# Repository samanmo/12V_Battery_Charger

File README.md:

# 12V Half-Bridge LLC Battery Charger | KiCad Designer

A high-efficiency **12V battery charger** designed for **240V AC mains input**, utilizing a Power Factor Correction (PFC) front-end and a Half-Bridge LLC resonant converter controlled by an STM32 microcontroller.

> **⚠️ HIGH VOLTAGE WARNING:** This design interfaces directly with 240V AC mains and generates lethal high-voltage DC buses. Do not build, test, or probe this hardware unless you are qualified to work with high-voltage power electronics and follow proper isolation procedures (e.g., using an isolation transformer and differential probes).

---

## Key Features & Architecture

Based on the hierarchical schematic blocks in this repository, the power stage and control architecture include:

* **AC Input & EMI Filtering (`emf_filter.kicad_sch`):** Mains input protection, inrush current limiting (NTC/PTC), varistors, and common/differential mode chokes.
* **Half-Bridge LLC Resonant Stage (`llc_power.kicad_sch`):** High-frequency resonant tank with custom transformer and isolated gate drivers (`UCC256404`).
* **Secondary Rectification & Output (`secondary_power.kicad_sch`, `output_filtering.kicad_sch`, `output_protection.kicad_sch`):** Secondary rectification, LC output filtering, and reverse polarity / over-voltage / over-current protection (`ACS720` current sensing).
* **Auxiliary & Bias Power (`auxiliary_power.kicad_sch`, `bias_power_supply.kicad_sch`):** Dedicated auxiliary supplies powering primary and secondary control ICs.
* **Digital Control & Monitoring (`STM32Controller.kicad_sch`, `temperature_sensing.kicad_sch`):** STM32-based PWM generation, charging profile control (CC/CV), and thermal monitoring.

---

## Repository Structure

```text
├── 2025_11_17_ver6.0.kicad_pro    # Main KiCad project file
├── 2025_11_17_ver6.0.kicad_sch    # Root hierarchical schematic
├── 2025_11_17_ver6.0.kicad_pcb    # Main PCB layout
├── *.kicad_sch                    # Hierarchical sub-schematics (PFC, LLC, STM32, etc.)
├── *.kicad_sym                    # Project-specific custom symbol libraries
├── *.pretty/                      # Project-specific custom footprint libraries
├── sym-lib-table & fp-lib-table   # Local library path mappings
├── BatteryCharger_pdf/            # Exported schematic/documentation PDFs
├── 2025_11_17_ver6.0.xlsx         # Bill of Materials (BOM)
└── Design Rules.txt               # PCB layout & clearance design rules
```

---

## Getting Started

1. **Clone the repository:**
   ```bash
   git clone https://github.com/samanmo/12V_Battery_Charger.git
   ```
2. **Open in KiCad:**
   * Launch KiCad and open `2025_11_17_ver6.0.kicad_pro`.
   * All custom symbols (`.kicad_sym`) and footprints (`.pretty`) are stored locally inside the repository and mapped via `sym-lib-table` and `fp-lib-table`.

---

## Renders & Schematics
<!-- 
*(Tip: Export a 3D render from KiCad's 3D Viewer as `docs/pcb_3d.png` and uncomment the line below to display it here)*
-->
<!--  -->

* Full schematic PDFs are available in the [`BatteryCharger_pdf/`](./BatteryCharger_pdf) directory.

---

## License

This project is licensed under the **MIT License** — see the [LICENSE](./LICENSE) file for details.

# 12V ハーフブリッジLLC バッテリーチャージャー
240V AC商用電源入力向けに設計された高効率な12Vバッテリーチャージャーです。力率改善（PFC）フロントエンドと、STM32マイクロコントローラによって制御されるハーフブリッジLLC共振コンバータを採用しています。
> **⚠️ 高電圧に関する警告:**  本設計は240V AC商用電源に直接接続され、致死的な高電圧DCバスを生成します。高電圧パワーエレクトロニクスを取り扱う資格を有し、適切な絶縁手順（絶縁トランスや差動プローブの使用など）を遵守できる場合を除き, 本ハードウェアの製作、テスト、またはプロービングを行わないでください。

---

## 主な特徴とアーキテクチャ
本リポジトリ内の階層型回路図ブロックに基づく、パワーステージおよび制御アーキテクチャの構成は以下の通りです：

* **AC入力およびEMIフィルタリング (emf_filter.kicad_sch)：** 商用電源入力保護、突入電流制限（NTC/PTC）、バリスタ、およびコモンモード／ノーマルモードチョークコイルを備えています。

* **ハーフブリッジLLC共振ステージ (llc_power.kicad_sch)：** カスタムトランスと絶縁型ゲートドライバ（UCC256404）を使用した高周波共振タンクです。

* **二次側整流および出力 (secondary_power.kicad_sch, output_filtering.kicad_sch, output_protection.kicad_sch)：** 二次側整流、LC出力フィルタリング、および逆接続・過電圧・過電流保護（ACS720電流センシング）を搭載しています。

* **補助電源およびバイアス電源 (auxiliary_power.kicad_sch, bias_power_supply.kicad_sch)：** 一次側および二次側の制御ICに電力を供給する専用の補助電源です。

* **デジタル制御および監視 (STM32Controller.kicad_sch, temperature_sensing.kicad_sch)：** STM32ベースのPWM生成、充電プロファイル制御（CC/CV）、および温度監視を行います。

## リポジトリ構成

```text
├── 2025_11_17_ver6.0.kicad_pro    # メインKiCadプロジェクトファイル
├── 2025_11_17_ver6.0.kicad_sch    # ルート階層回路図
├── 2025_11_17_ver6.0.kicad_pcb    # メインPCBレイアウト
├── *.kicad_sch                    # 階層サブ回路図（PFC、LLC、STM32など）
├── *.kicad_sym                    # プロジェクト固有のカスタムシンボルライブラリ
├── *.pretty/                      # プロジェクト固有のカスタムフットプリントライブラリ
├── sym-lib-table & fp-lib-table   # ローカルライブラリパスマッピング
├── BatteryCharger_pdf/            # エクスポートされた回路図・ドキュメントPDF
├── 2025_11_17_ver6.0.xlsx         # 部品表（BOM）
└── Design Rules.txt               # PCBレイアウトおよびクリアランス設計ルール

---

## はじめに
1. **リポジトリのクローン：**
```bash
	git clone https://github.com
```

2. **KiCadで開く：**
	* KiCadを起動し、2025_11_17_ver6.0.kicad_pro を開きます。
	* すべてのカスタムシンボル（.kicad_sym）およびフットプリント（.pretty）はリポジトリ内にローカル保存されており、sym-lib-table および fp-lib-table を介してマッピングされています。
---

## レンダリングと回路図
	* 完全な回路図PDFは BatteryCharger_pdf/ ディレクトリにあります。

---
## ライセンス (License)

このプロジェクトは [MITライセンス](LICENSE) の下で公開されています。

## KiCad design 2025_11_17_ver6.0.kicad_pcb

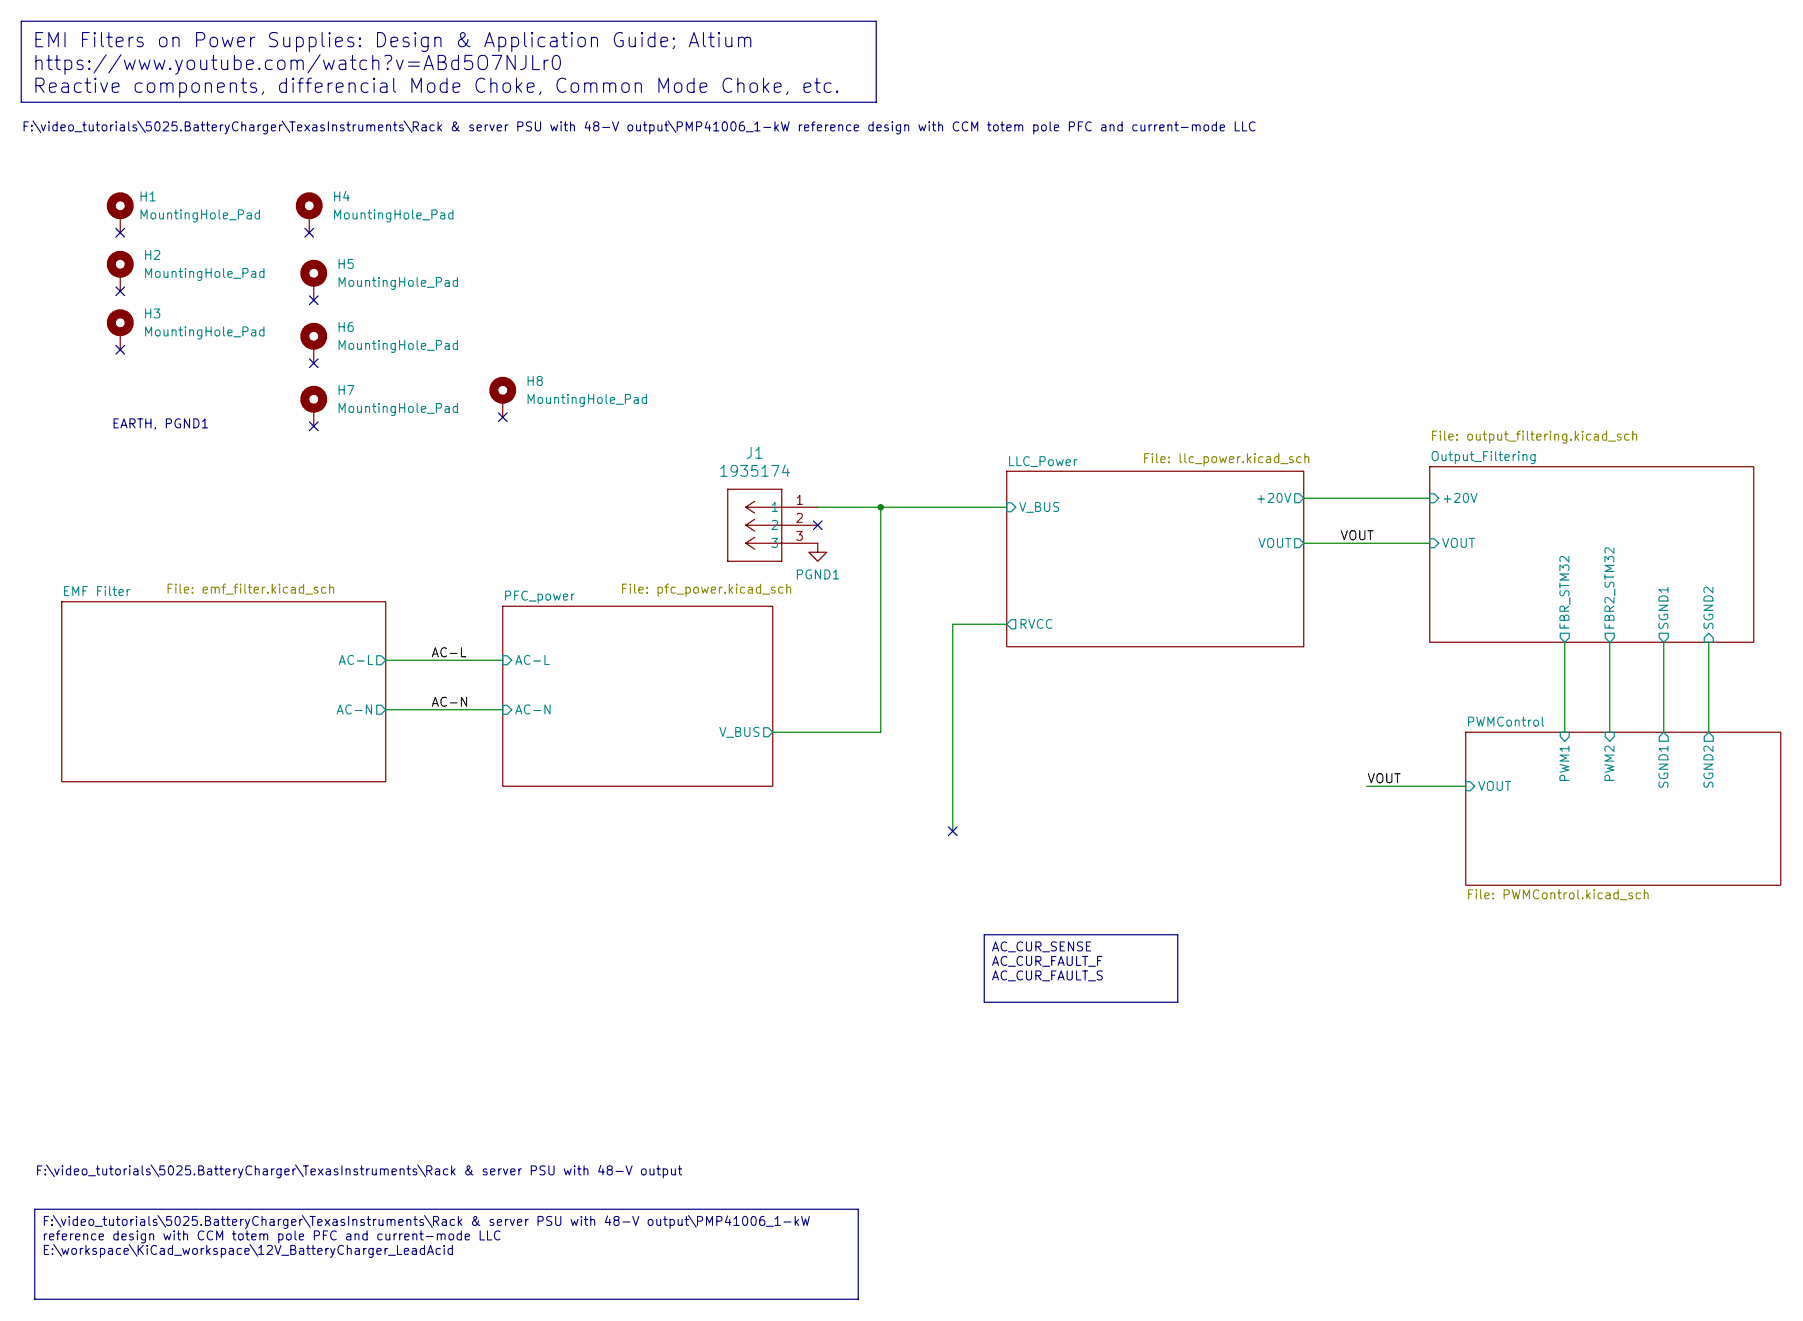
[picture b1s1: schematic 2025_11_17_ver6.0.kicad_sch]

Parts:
H1, H2, H3, H4, H5, H6, H7, H8: MountingHole_Pad; MountingHole_3mm_Pad
J1: 1935174; CONN_1935174_PXC; Manufacturer_Part_Number 1935174; Digi-Key_PN 277-1578-ND

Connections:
/LLC_Power/V_BUS: J1.1; also elsewhere on the board
PGND1: J1.3; also elsewhere on the board

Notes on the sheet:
F:\video_tutorials\5025.BatteryCharger\TexasInstruments\Rack & server PSU with 48-V output
EARTH, PGND1
F:\video_tutorials\5025.BatteryCharger\TexasInstruments\Rack & server PSU with 48-V output\PMP41006_1-kW reference design with CCM totem pole PFC and current-mode LLC
AC_CUR_SENSE AC_CUR_FAULT_F AC_CUR_FAULT_S
F:\video_tutorials\5025.BatteryCharger\TexasInstruments\Rack & server PSU with 48-V output\PMP41006_1-kW reference design with CCM totem pole PFC and current-mode LLC E:\workspace\KiCad_workspace\12V_BatteryCharger_LeadAcid
EMI Filters on Power Supplies: Design & Application Guide; Altium https://www.youtube.com/watch?v=ABd5O7NJLr0 Reactive components, differencial Mode Choke, Common Mode Choke, etc.

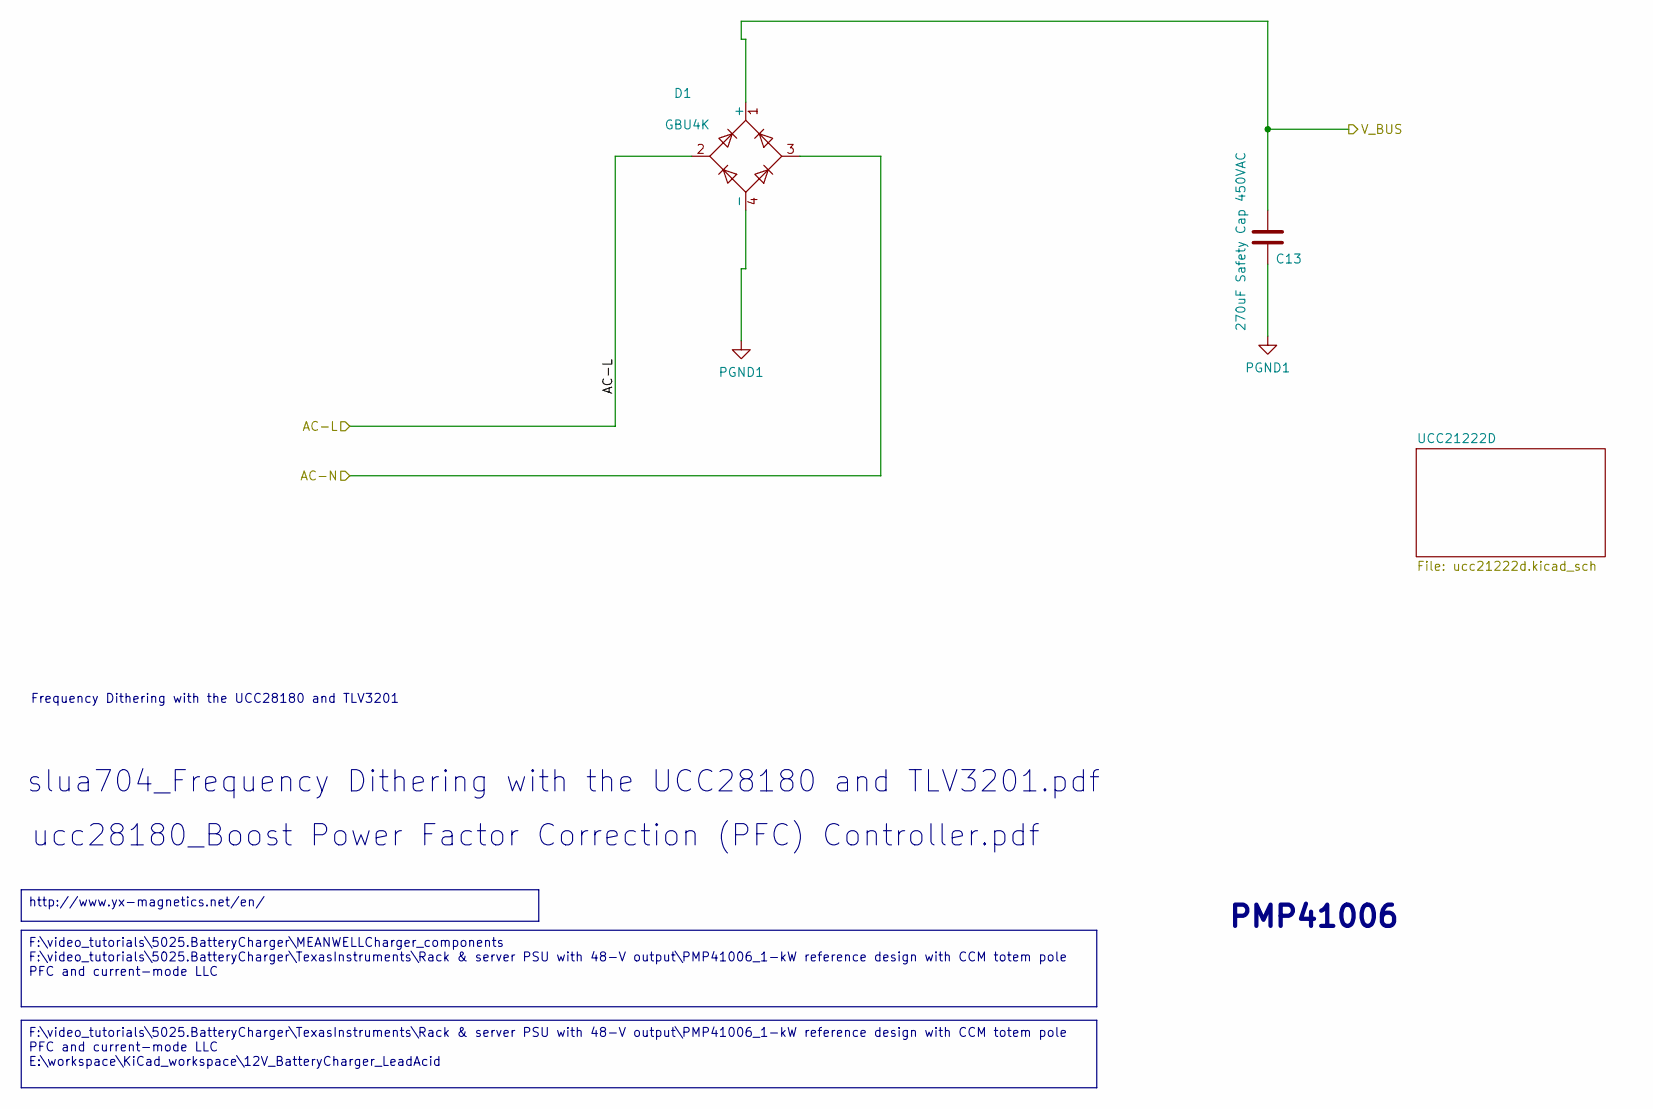
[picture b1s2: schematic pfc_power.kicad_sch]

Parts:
C13: 270uF Safety Cap 450VAC; CP_Radial_D22.0mm_P10.00mm_SnapIn; Mouser Part Number 871-B32923C3155M189; Digi-Key_PN 495-4938-1-ND
D1: GBU4K; Diode_Bridge_Vishay_GBU; Manufacturer_Part_Number GBU4K-E3/45; Digi-Key_PN GBU4K-E3/45GI-ND

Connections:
/AC-L: D1.2; also elsewhere on the board
/AC-N: D1.3; also elsewhere on the board
/LLC_Power/V_BUS: C13.1, D1.1 (+); also elsewhere on the board
PGND1: C13.2, D1.4 (-); also elsewhere on the board

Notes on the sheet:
PMP41006
ucc28180_Boost Power Factor Correction (PFC) Controller.pdf
slua704_Frequency Dithering with the UCC28180 and TLV3201.pdf
Frequency Dithering with the UCC28180 and TLV3201
F:\video_tutorials\5025.BatteryCharger\MEANWELLCharger_components F:\video_tutorials\5025.BatteryCharger\TexasInstruments\Rack & server PSU with 48-V output\PMP41006_1-kW reference design with CCM totem pole PFC and current-mode LLC
http://www.yx-magnetics.net/en/
F:\video_tutorials\5025.BatteryCharger\TexasInstruments\Rack & server PSU with 48-V output\PMP41006_1-kW reference design with CCM totem pole PFC and current-mode LLC E:\workspace\KiCad_workspace\12V_BatteryCharger_LeadAcid

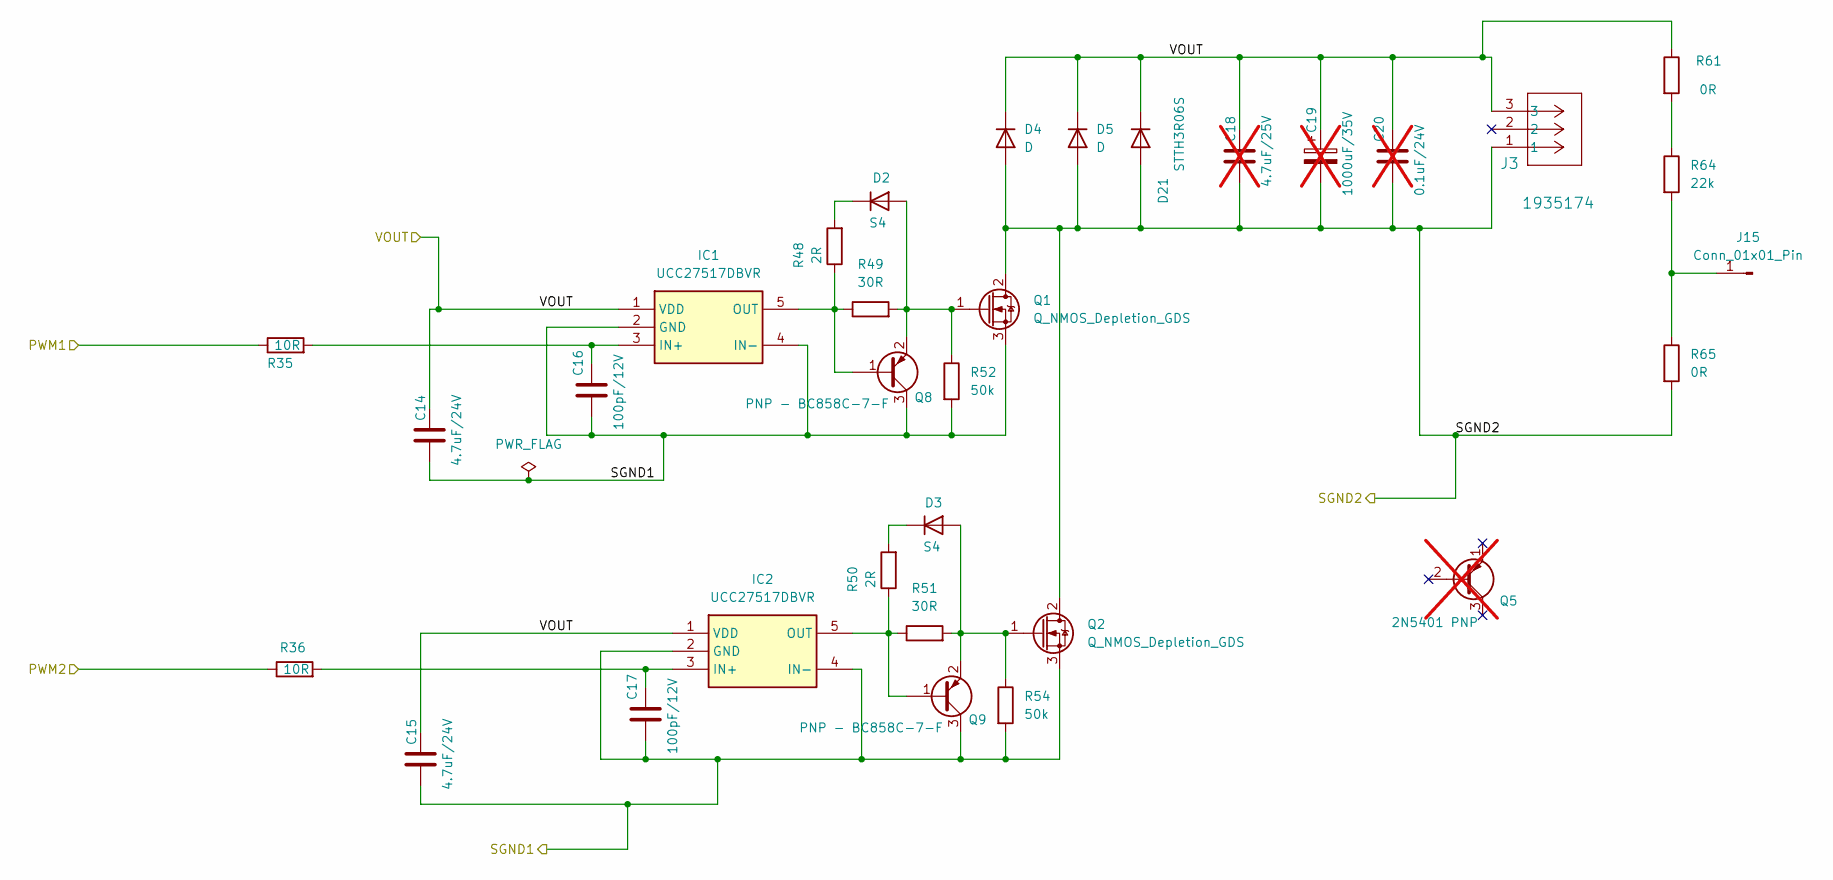
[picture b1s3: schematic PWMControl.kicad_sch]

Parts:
C14, C15: 4.7uF/24V; C_0805_2012Metric_Pad1.18x1.45mm_HandSolder; Manufacturer_Part_Number GRT21BR61H475KE13L; Digi-Key_PN 490-12394-1-ND
C16, C17: 100pF/12V; C_0805_2012Metric_Pad1.18x1.45mm_HandSolder; Manufacturer_Part_Number CC0805KRX7R9BB104; Digi-Key_PN 311-1140-1-ND
C18: 4.7uF/25V; C_0805_2012Metric_Pad1.18x1.45mm_HandSolder; Manufacturer_Part_Number GRT21BR61H475KE13L; Digi-Key_PN 490-12394-1-ND; not fitted
C19: 1000uF/35V; C_Radial_D12.5mm_H25.0mm_P5.00mm; Manufacturer_Part_Number ECA-1HM102; Digi-Key_PN P5186-ND; not fitted
C20: 0.1uF/24V; C_0805_2012Metric_Pad1.18x1.45mm_HandSolder; Manufacturer_Part_Number CC0805KRX7R9BB104; Digi-Key_PN 311-1140-1-ND; not fitted
D2, D3: S4; D_0805_2012Metric_Pad1.15x1.40mm_HandSolder; Manufacturer_Part_Number BAS316Z; Digi-Key_PN 1727-7370-1-ND
D4, D5: D; D_SMA_Handsoldering
D21: STTH3R06S; D_SMC_Handsoldering; Manufacturer_Part_Number STTH3R06S; Digi-Key_PN 497-3779-1-ND
IC1, IC2: UCC27517DBVR; SOT-23-5_HandSoldering; Mouser Part Number 595-UCC27517DBVR
J3: 1935174; TerminalBlock_Phoenix_PT-1,5-3-5.0-H_1x03_P5.00mm_Horizonta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; Manufacturer_Part_Number 1935174; Digi-Key_PN 277-1578-ND
J15: Conn_01x01_Pin; PinHeader_1x01_P2.54mm_Vertical
Q1, Q2: Q_NMOS_Depletion_GDS; TO-220-3_Vertical
Q5: 2N5401 PNP; TO-92L_Inline_Wide; not fitted
Q8, Q9: PNP - BC858C-7-F; SOT-23; Manufacturer_Part_Number BC858C-7-F; Digi-Key_PN 31-BC858C-7-FCT-ND
R35, R36: 10R; R_0805_2012Metric_Pad1.20x1.40mm_HandSolder
R48, R50: 2R; R_1206_3216Metric_Pad1.30x1.75mm_HandSolder; Manufacturer_Part_Number RT1206DRE0710RL; Digi-Key_PN 311-2958-1-ND
R49, R51: 30R; R_1206_3216Metric_Pad1.30x1.75mm_HandSolder
R52, R54: 50k; R_0805_2012Metric_Pad1.20x1.40mm_HandSolder
R61, R65: 0R; R_0805_2012Metric_Pad1.20x1.40mm_HandSolder
R64: 22k; R_0805_2012Metric_Pad1.20x1.40mm_HandSolder

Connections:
/Output_Filtering/FBR2_STM32: R36.1; also elsewhere on the board
/Output_Filtering/FBR_STM32: R35.1; also elsewhere on the board
/Output_Filtering/SGND1: C14.2, C15.2, C16.2, C17.2, IC1.2 (GND), IC1.4 (IN-), IC2.2 (GND), IC2.4 (IN-), Q1.3 (S), Q2.3 (S), Q8.3 (C), Q9.3 (C), R52.2, R54.2; also elsewhere on the board
/Output_Filtering/SGND2: C18.2, C19.2, C20.2, D4.2 (A), D5.2 (A), D21.2 (A), J3.1, Q1.2 (D), Q2.2 (D), R65.2; also elsewhere on the board
/VOUT: C14.1, C15.1, C18.1, C19.1, C20.1, D4.1 (K), D5.1 (K), D21.1 (K), IC1.1 (VDD), IC2.1 (VDD), J3.3, R61.1; also elsewhere on the board
unnamed: D2.2 (A), Q1.1 (G), Q8.2 (E), R49.2, R52.1
unnamed: D2.1 (K), R48.2
unnamed: D3.2 (A), Q2.1 (G), Q9.2 (E), R51.2, R54.1
unnamed: D3.1 (K), R50.2
unnamed: C16.1, IC1.3 (IN+), R35.2
unnamed: IC1.5 (OUT), Q8.1 (B), R48.1, R49.1
unnamed: C17.1, IC2.3 (IN+), R36.2
unnamed: IC2.5 (OUT), Q9.1 (B), R50.1, R51.1
unnamed: J15.1, R64.2, R65.1
unnamed: R61.2, R64.1

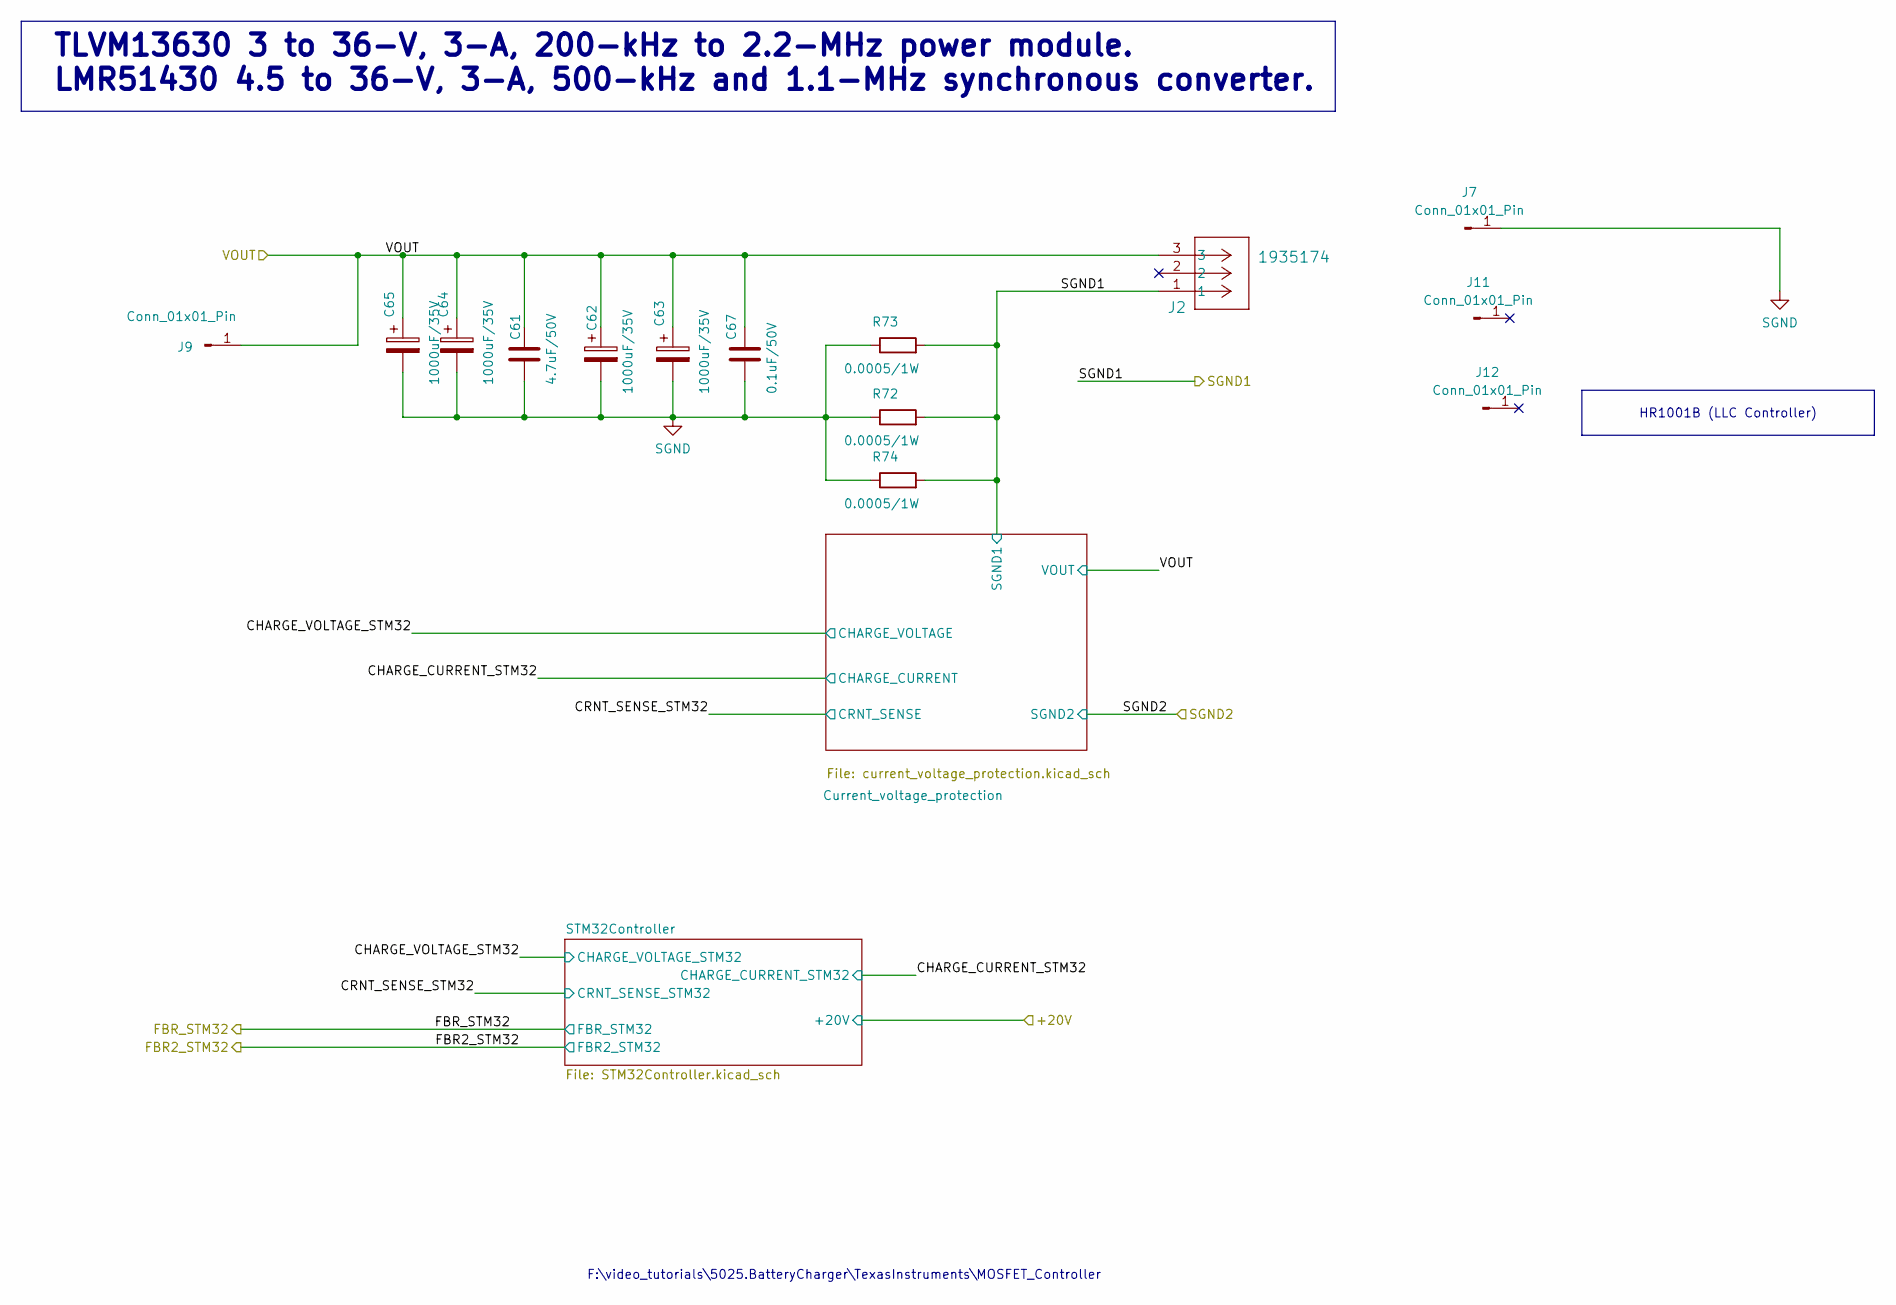
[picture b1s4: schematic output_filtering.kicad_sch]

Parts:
C61: 4.7uF/50V; C_0805_2012Metric_Pad1.18x1.45mm_HandSolder; Manufacturer_Part_Number GRT21BR61H475KE13L; Digi-Key_PN 490-12394-1-ND
C62, C63, C64, C65: 1000uF/35V; C_Radial_D12.5mm_H25.0mm_P5.00mm; Manufacturer_Part_Number ECA-1HM102; Digi-Key_PN P5186-ND
C67: 0.1uF/50V; C_0805_2012Metric_Pad1.18x1.45mm_HandSolder; Manufacturer_Part_Number CC0805KRX7R9BB104; Digi-Key_PN 311-1140-1-ND
J2: 1935174; CONN_1935174_PXC; Manufacturer_Part_Number 1935174; Digi-Key_PN 277-1578-ND
J7, J9, J11, J12: Conn_01x01_Pin; PinHeader_1x01_P2.54mm_Vertical
R72, R73, R74: 0.0005/1W; R_2512_6332Metric_Pad1.40x3.35mm_HandSolder; Manufacturer_Part_Number PA2512FKF7W0U5E; Digi-Key_PN 13-PA2512FKF7W0U5ECT-ND

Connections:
/Output_Filtering/SGND1: J2.1, R72.2, R73.2, R74.2; also elsewhere on the board
/VOUT: C61.1, C62.1, C63.1, C64.1, C65.1, C67.1, J2.3, J9.1; also elsewhere on the board
SGND: C61.2, C62.2, C63.2, C64.2, C65.2, C67.2, J7.1, R72.1, R73.1, R74.1; also elsewhere on the board

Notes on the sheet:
F:\video_tutorials\5025.BatteryCharger\TexasInstruments\MOSFET_Controller
TLVM13630 3 to 36-V, 3-A, 200-kHz to 2.2-MHz power module. LMR51430 4.5 to 36-V, 3-A, 500-kHz and 1.1-MHz synchronous converter.
HR1001B (LLC Controller)

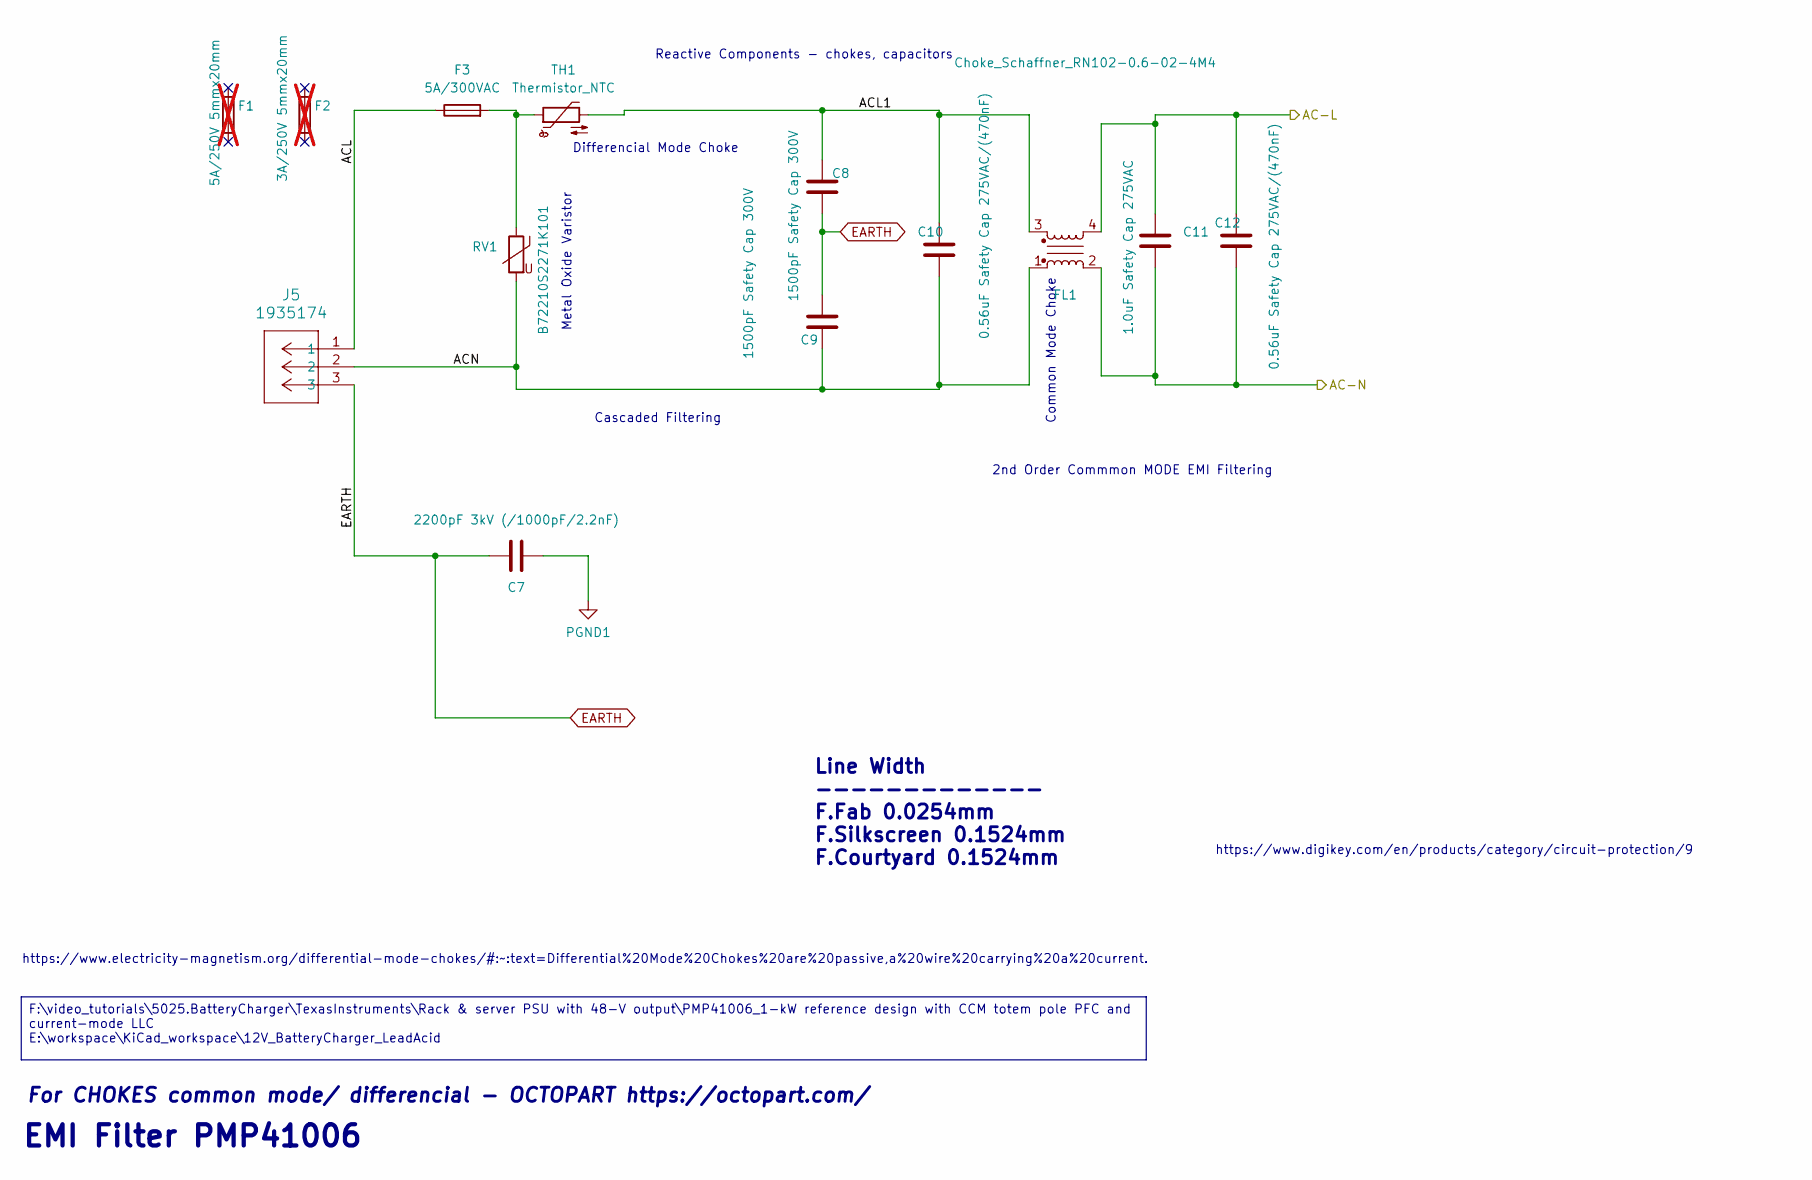
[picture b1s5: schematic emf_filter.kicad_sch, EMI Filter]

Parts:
C7: 2200pF 3kV (/1000pF/2.2nF); CK45B3FD222KYVNA; Mouser Part Number 810-CK45-B3FD222KYVN; Digi-Key_PN 445-CK45-B3FD222KYVNACT-ND
C8, C9: 1500pF Safety Cap 300V; C_Disc_D10.0mm_W2.5mm_P5.00mm; Mouser Part Number 80-R413D1150JMT0K; Digi-Key_PN 399-R413D1150JMT0K-ND
C10, C12: 0.56uF Safety Cap 275VAC/(470nF); C_Rect_L24.0mm_W7.0mm_P22.50mm_MKT; Mouser Part Number 80-R463I356040N0M; Digi-Key_PN 399-R413D1150JMT0K-ND
C11: 1.0uF Safety Cap 275VAC; C_Rect_L16.5mm_W8.7mm_P15.00mm_MKT; Mouser Part Number 871-B32923C3155M189; Digi-Key_PN 495-4938-1-ND
F1: 5A/250V 5mmx20mm; Manufacturer_Part_Number 0217005.HXP; Digi-Key_PN F2395-ND; not fitted
F2: 3A/250V 5mmx20mm; Manufacturer_Part_Number 0235003.HXP; Digi-Key_PN F2682-ND; not fitted
F3: 5A/300VAC; FUSE_4628_Keystone; Manufacturer_Part_Number 4628; Digi-Key_PN 36-4628-ND
FL1: Choke_Schaffner_RN102-0.6-02-4M4; Choke_Schaffner_RN102-04-7.0x10.0mm
J5: 1935174; CONN_1935174_PXC; Manufacturer_Part_Number 1935174; Digi-Key_PN 277-1578-ND
RV1: B72210S2271K101; Manufacturer_Part_Number B72210S2271K101; Digi-Key_PN 495-1433-ND
TH1: Thermistor_NTC; R_Axial_DIN0411_L9.9mm_D3.6mm_P12.70mm_Horizontal

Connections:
/AC-L: C11.1, C12.1, FL1.4; also elsewhere on the board
/AC-N: C11.2, C12.2, FL1.2; also elsewhere on the board
/EMF Filter/ACL: F3.1, J5.1
/EMF Filter/ACL1: C8.1, C10.1, FL1.3, TH1.2
/EMF Filter/ACN: C9.2, C10.2, FL1.1, J5.2, RV1.2
EARTH: C7.1, C8.2, C9.1, J5.3
unnamed: F3.2, RV1.1, TH1.1
PGND1: C7.2; also elsewhere on the board

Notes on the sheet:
2nd Order Commmon MODE EMI Filtering
For CHOKES common mode/ differencial - OCTOPART https://octopart.com/
Common Mode Choke
Metal Oxide Varistor
Differencial Mode Choke
EMI Filter PMP41006
Reactive Components - chokes, capacitors
https://www.digikey.com/en/products/category/circuit-protection/9
Cascaded Filtering
https://www.electricity-magnetism.org/differential-mode-chokes/#:~:text=Differential%20Mode%20Chokes%20are%20passive,a%20wire%20carrying%20a%20current.
Line Width ------------- F.Fab 0.0254mm F.Silkscreen 0.1524mm F.Courtyard 0.1524mm
F:\video_tutorials\5025.BatteryCharger\TexasInstruments\Rack & server PSU with 48-V output\PMP41006_1-kW reference design with CCM totem pole PFC and current-mode LLC E:\workspace\KiCad_workspace\12V_BatteryCharger_LeadAcid

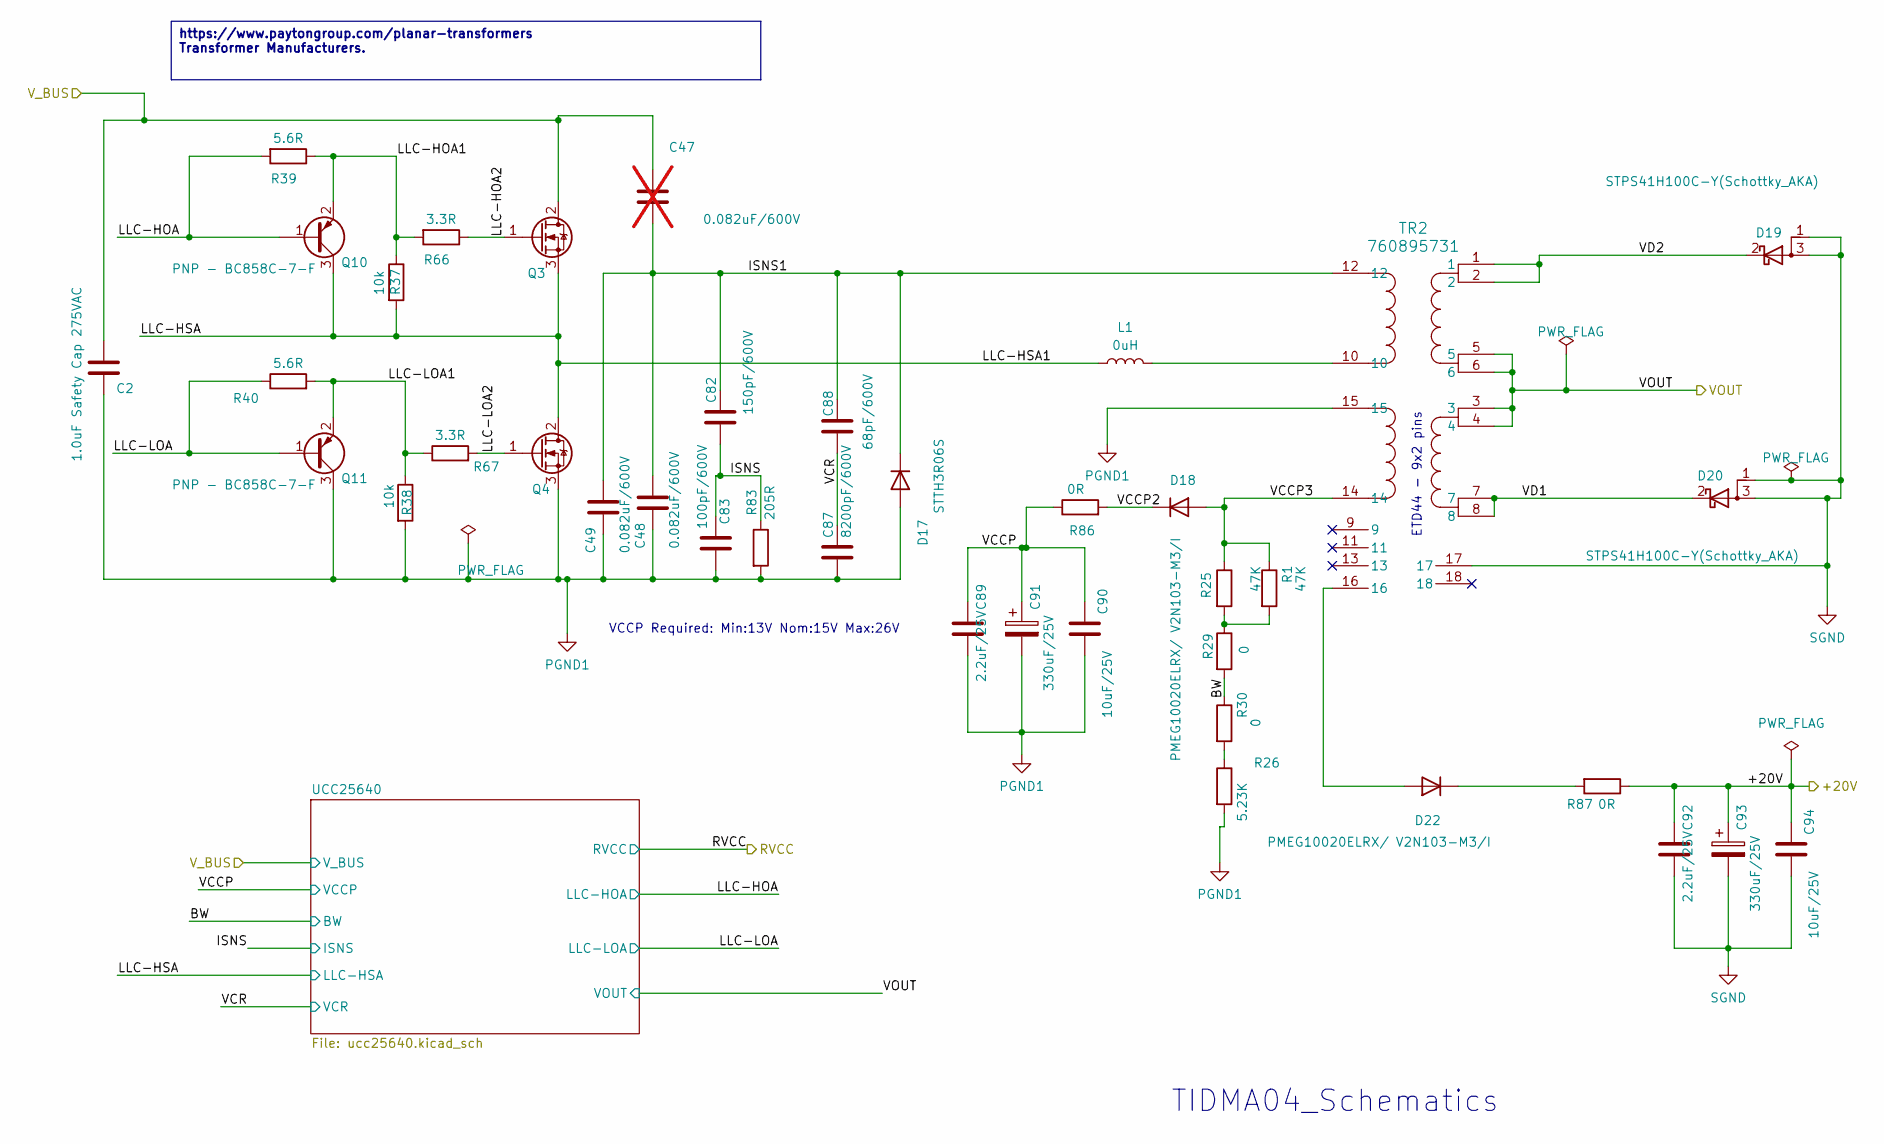
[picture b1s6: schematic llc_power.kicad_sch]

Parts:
C2: 1.0uF Safety Cap 275VAC; C_Rect_L16.5mm_W8.7mm_P15.00mm_MKT; Mouser Part Number 871-B32923C3155M189; Digi-Key_PN 495-4938-1-ND
C47: 0.082uF/600V; C_Rect_L18.0mm_W6.0mm_P15.00mm_FKS3_FKP3; Manufacturer_Part_Number B32642B0153J; Digi-Key_PN 495-7138-ND; not fitted
C48, C49: 0.082uF/600V; C_Rect_L18.0mm_W6.0mm_P15.00mm_FKS3_FKP3; Manufacturer_Part_Number B32642B0153J; Digi-Key_PN 495-7138-ND
C82: 150pF/600V; C_Rect_L7.2mm_W4.5mm_P5.00mm_FKS2_FKP2_MKS2_MKP2; Manufacturer_Part_Number R76UI0150SE40J; Digi-Key_PN 399-R76UI0150SE40J-ND
C83: 100pF/600V; C_Rect_L7.2mm_W4.5mm_P5.00mm_FKS2_FKP2_MKS2_MKP2; Manufacturer_Part_Number R76UI01004040J; Digi-Key_PN 399-12614-ND
C87: 8200pF/600V; C_Rect_L18.0mm_W6.0mm_P15.00mm_FKS3_FKP3; Manufacturer_Part_Number B32672L8822J000; Digi-Key_PN 495-3231-ND
C88: 68pF/600V; C_Rect_L7.2mm_W4.5mm_P5.00mm_FKS2_FKP2_MKS2_MKP2; Manufacturer_Part_Number FKP2O100681D00KSSD; Digi-Key_PN 1928-1290-ND
C89, C92: 2.2uF/25V; C_0805_2012Metric_Pad1.18x1.45mm_HandSolder; Manufacturer_Part_Number CL21B225KAFNFNE; Digi-Key_PN 1276-2953-1-ND
C90, C94: 10uF/25V; C_0805_2012Metric_Pad1.18x1.45mm_HandSolder; Manufacturer_Part_Number TMK212BBJ106KG-T; Digi-Key_PN 587-2985-1-ND
C91, C93: 330uF/25V; PCAP_8x10-ELECT_NCA-M; Manufacturer_Part_Number UWT1E331MNL1GS; Digi-Key_PN 493-2193-1-ND
D17: STTH3R06S; D_SMC_Handsoldering; Manufacturer_Part_Number STTH3R06S; Digi-Key_PN 497-3779-1-ND
D18, D22: PMEG10020ELRX/ V2N103-M3/I; Nexperia_CFP3_SOD-123W; Manufacturer_Part_Number PMEG10020ELRX; Digi-Key_PN 1727-2396-1-ND
D19, D20: STPS41H100C-Y(Schottky_AKA); TO-220-3_Vertical; Manufacturer_Part_Number STPS41H100CTY; Digi-Key_PN 497-15565-5-ND
L1: 0uH; B32642B0153J_largeHoles
Q3, Q4: STW56N60DM2/TK39A60W / TK040N65Z; TO-220-3_Vertical; Manufacturer_Part_Number STW56N60DM2; Digi-Key_PN 497-16341-5-ND
Q10, Q11: PNP - BC858C-7-F; SOT-23; Manufacturer_Part_Number BC858C-7-F; Digi-Key_PN 31-BC858C-7-FCT-ND
R1, R25: 47K; R_0805_2012Metric_Pad1.20x1.40mm_HandSolder; Manufacturer_Part_Number RC0805FR-07549KL; Digi-Key_PN 311-549KCRCT-ND
R26: 5.23K; R_0805_2012Metric_Pad1.20x1.40mm_HandSolder; Manufacturer_Part_Number RC0805FR-07140KL; Digi-Key_PN 311-140KCRCT-ND
R29, R30: 0; R_0805_2012Metric_Pad1.20x1.40mm_HandSolder; Manufacturer_Part_Number RC0805FR-07549KL; Digi-Key_PN 311-549KCRCT-ND
R37, R38: 10k; R_0805_2012Metric_Pad1.20x1.40mm_HandSolder; Manufacturer_Part_Number RC0805FR-07100KL; Digi-Key_PN 311-100KCRCT-ND
R39, R40: 5.6R; R_1206_3216Metric_Pad1.30x1.75mm_HandSolder; Manufacturer_Part_Number RC1206FR-074R99L; Digi-Key_PN 311-4.99FRCT-ND
R66, R67: 3.3R; R_1206_3216Metric_Pad1.30x1.75mm_HandSolder; Manufacturer_Part_Number RC1206FR-074R99L; Digi-Key_PN 311-4.99FRCT-ND
R83: 205R; R_1206_3216Metric_Pad1.30x1.75mm_HandSolder; Manufacturer_Part_Number RC1206FR-07205RL; Digi-Key_PN 311-205FRCT-ND
R86, R87: 0R; R_0805_2012Metric_Pad1.20x1.40mm_HandSolder; Manufacturer_Part_Number RC0805JR-070RL; Digi-Key_PN 311-0.0ARCT-ND
TR2: 760895731; CONN16_895741_WRE_Extended_SecondaryBigPins; Manufacturer_Part_Number 760895741; Digi-Key_PN 732-5069-ND

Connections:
/LLC_Power/+20V: C92.1, C93.1, C94.1, R87.1; also elsewhere on the board
/LLC_Power/BW: R29.2, R30.1; also elsewhere on the board
/LLC_Power/ISNS: C82.2, C83.1, R83.1; also elsewhere on the board
/LLC_Power/ISNS1: C47.2, C48.1, C49.1, C82.1, C88.1, D17.1 (K), TR2.12
/LLC_Power/LLC-HOA: Q10.1 (B), R39.2; also elsewhere on the board
/LLC_Power/LLC-HOA1: Q10.2 (E), R37.1, R39.1, R66.2
/LLC_Power/LLC-HOA2: Q3.1 (G), R66.1
/LLC_Power/LLC-HSA: L1.1, Q3.3 (S), Q4.2 (D), Q10.3 (C), R37.2; also elsewhere on the board
/LLC_Power/LLC-LOA: Q11.1 (B), R40.1; also elsewhere on the board
/LLC_Power/LLC-LOA1: Q11.2 (E), R38.1, R40.2, R67.1
/LLC_Power/LLC-LOA2: Q4.1 (G), R67.2
/LLC_Power/VCCP: C89.1, C90.1, C91.1, R86.1; also elsewhere on the board
/LLC_Power/VCCP2: D18.1 (K), R86.2
/LLC_Power/VCCP3: D18.2 (A), R1.1, R25.1, TR2.14
/LLC_Power/VCR: C87.1, C88.2; also elsewhere on the board
/LLC_Power/VD1: D20.2 (K), TR2.7, TR2.8
/LLC_Power/VD2: D19.2 (K), TR2.1, TR2.2
/LLC_Power/V_BUS: C2.1, C47.1, Q3.2 (D); also elsewhere on the board
/VOUT: TR2.3, TR2.4, TR2.5, TR2.6; also elsewhere on the board
unnamed: D22.2 (A), TR2.16
unnamed: D22.1 (K), R87.2
unnamed: L1.2, TR2.10
unnamed: R1.2, R25.2, R29.1
unnamed: R26.1, R30.2
PGND1: C2.2, C48.2, C49.2, C83.2, C87.2, C89.2, C90.2, C91.2, D17.2 (A), Q4.3 (S), Q11.3 (C), R26.2, R38.2, R83.2, TR2.15; also elsewhere on the board
SGND: C92.2, C93.2, C94.2, D19.1 (A), D19.3 (A), D20.1 (A), D20.3 (A), TR2.17; also elsewhere on the board

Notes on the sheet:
TIDMA04_Schematics
VCCP Required: Min:13V Nom:15V Max:26V
ETD44 - 9x2 pins
https://www.paytongroup.com/planar-transformers Transformer Manufacturers.
